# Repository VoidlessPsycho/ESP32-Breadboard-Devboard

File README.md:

# ESP32 Breadboard Devboard

This project is an ESP32-S3-WROOM-1 devboard that can fit on a breadboard, unlike standard ESP32 DevKit V1s. I made it because my current ESP32s don't fit on a breadboard and it makes it really difficult to prototype easily, so this fixes that problem.

[Journal](JOURNAL.md)

## Features
- ESP32-S3-WROOM-1 Microcontroller
- 33 GPIO Pins
- 2 3.3V Pins
- 1 VCC Pin (5-12V)
- Reset + Boot Buttons
- USB-C Receptacle
- Cool Art!

## Tech Stack:
- KiCad (PCB Design)
- Onshape (CAD Renders)
- Inkscape (SVG Art Drawing)
- VS Code (Documentation)

## Images
Schematic: \

PCB: \

CAD (Back): \

## Bill of Materials
| Manufacturer | Description | Qty | Total Price | Link |
| :--- | :--- | :---: | :--- | :--- |
| Samsung | 10uF 10V X5R 0603 Ceramic Capacitor | 6 | $0.26 | [C19702](https://jlcpcb.com/partdetail/20411-CL10A106KP8NNNC/C19702) |
| Samsung | 1uF 25V X5R 0402 Ceramic Capacitor | 2 | $0.04 | [C52923](https://jlcpcb.com/partdetail/53938-CL05A105KA5NQNC/C52923) |
| Samsung | 100nF 16V X7R 0402 Ceramic Capacitor | 6 | $0.01 | [C1525](https://jlcpcb.com/partdetail/1877-CL05B104KO5NNNC/C1525) |
| Jiangsu Changjing | B5819WSL 1A 40V SOD-123 Schottky Diode | 2 | $0.06 | [C8598](https://jlcpcb.com/partdetail/9093-B5819WSL/C8598) |
| Hubei KENTO | Red LED Water Clear 0603 | 2 | $0.01 | [C2286](https://jlcpcb.com/partdetail/Hubei_KENTOElec-KT0603R/C2286) |
| UNI-ROYAL | 0Ω 0402 Thick Film Resistor | 2 | $0.01 | [C17168](https://jlcpcb.com/partdetail/17853-0402WGF0000TCE/C17168) |
| UNI-ROYAL | 5.1kΩ 0402 1% Resistor | 4 | $0.01 | [C25905](https://jlcpcb.com/partdetail/26648-0402WGF5101TCE/C25905) |
| UNI-ROYAL | 2.2kΩ 0402 1% Resistor | 2 | $0.01 | [C25879](https://jlcpcb.com/partdetail/26622-0402WGF2201TCE/C25879) |
| UNI-ROYAL | 10kΩ 0402 1% Resistor | 4 | $0.01 | [C25744](https://jlcpcb.com/partdetail/26487-0402WGF1002TCE/C25744) |
| XUNPU | 4x3mm SMD Tactile Switch (Button) | 4 | $0.22 | [C720477](https://jlcpcb.com/partdetail/XUNPU-TS_1088AR02016/C720477) |
| STMicroelectronics| USBLC6-2SC6 SOT-23-6 ESD Protection | 5 | $0.83 | [C7519](https://jlcpcb.com/partdetail/STMicroelectronics-USBLC62SC6/C7519) |
| Advanced Monolithic | AMS1117-3.3V 1A LDO SOT-223 | 2 | $0.40 | [C6186](https://jlcpcb.com/partdetail/Advanced_MonolithicSystems-AMS1117_33/C6186) |
| Korean Hroparts | Type-C 16-Pin Female SMD USB Connector | 2 | $0.37 | [C165948](https://jlcpcb.com/partdetail/Korean_HropartsElec-TYPE_C_31_M12/C165948) |
| Espressif Systems | ESP32 Wi-Fi & Bluetooth Module | 1 | $4.77 | [C2913198](https://www.lcsc.com/product-detail/C2913198.html) |
| BOOMELE | 1x20P 2.54mm Pin Header | 5 | $0.78 | [C50981](https://www.lcsc.com/product-detail/C50981.html) |

<br>

### Manufacturing & Cost Summary

| Item / Service | Qty | Price |
| :--- | :---: | :--- |
| **PCB Manufacturing** (JLCPCB) | 5 | $2.00 |
| **PCB Assembly / PCBA** (JLCPCBA) | 2 | $19.15 |
| **Components Subtotal** | - | $7.79 |=
| JLCPCB Shipping (GSDL) | - | $3.12 |
| LCSC Shipping (GSDL) | - | $8.00 |
| LCSC Handling Fee | - | $5.00 |
| **Total Project Cost** | | **$42.82** |

---

## Motivation
I made this project to make ESP32 modules usable on a devboard. It also helped me develop my PCB skills. I also want to present my design at Open Sauce 2026.

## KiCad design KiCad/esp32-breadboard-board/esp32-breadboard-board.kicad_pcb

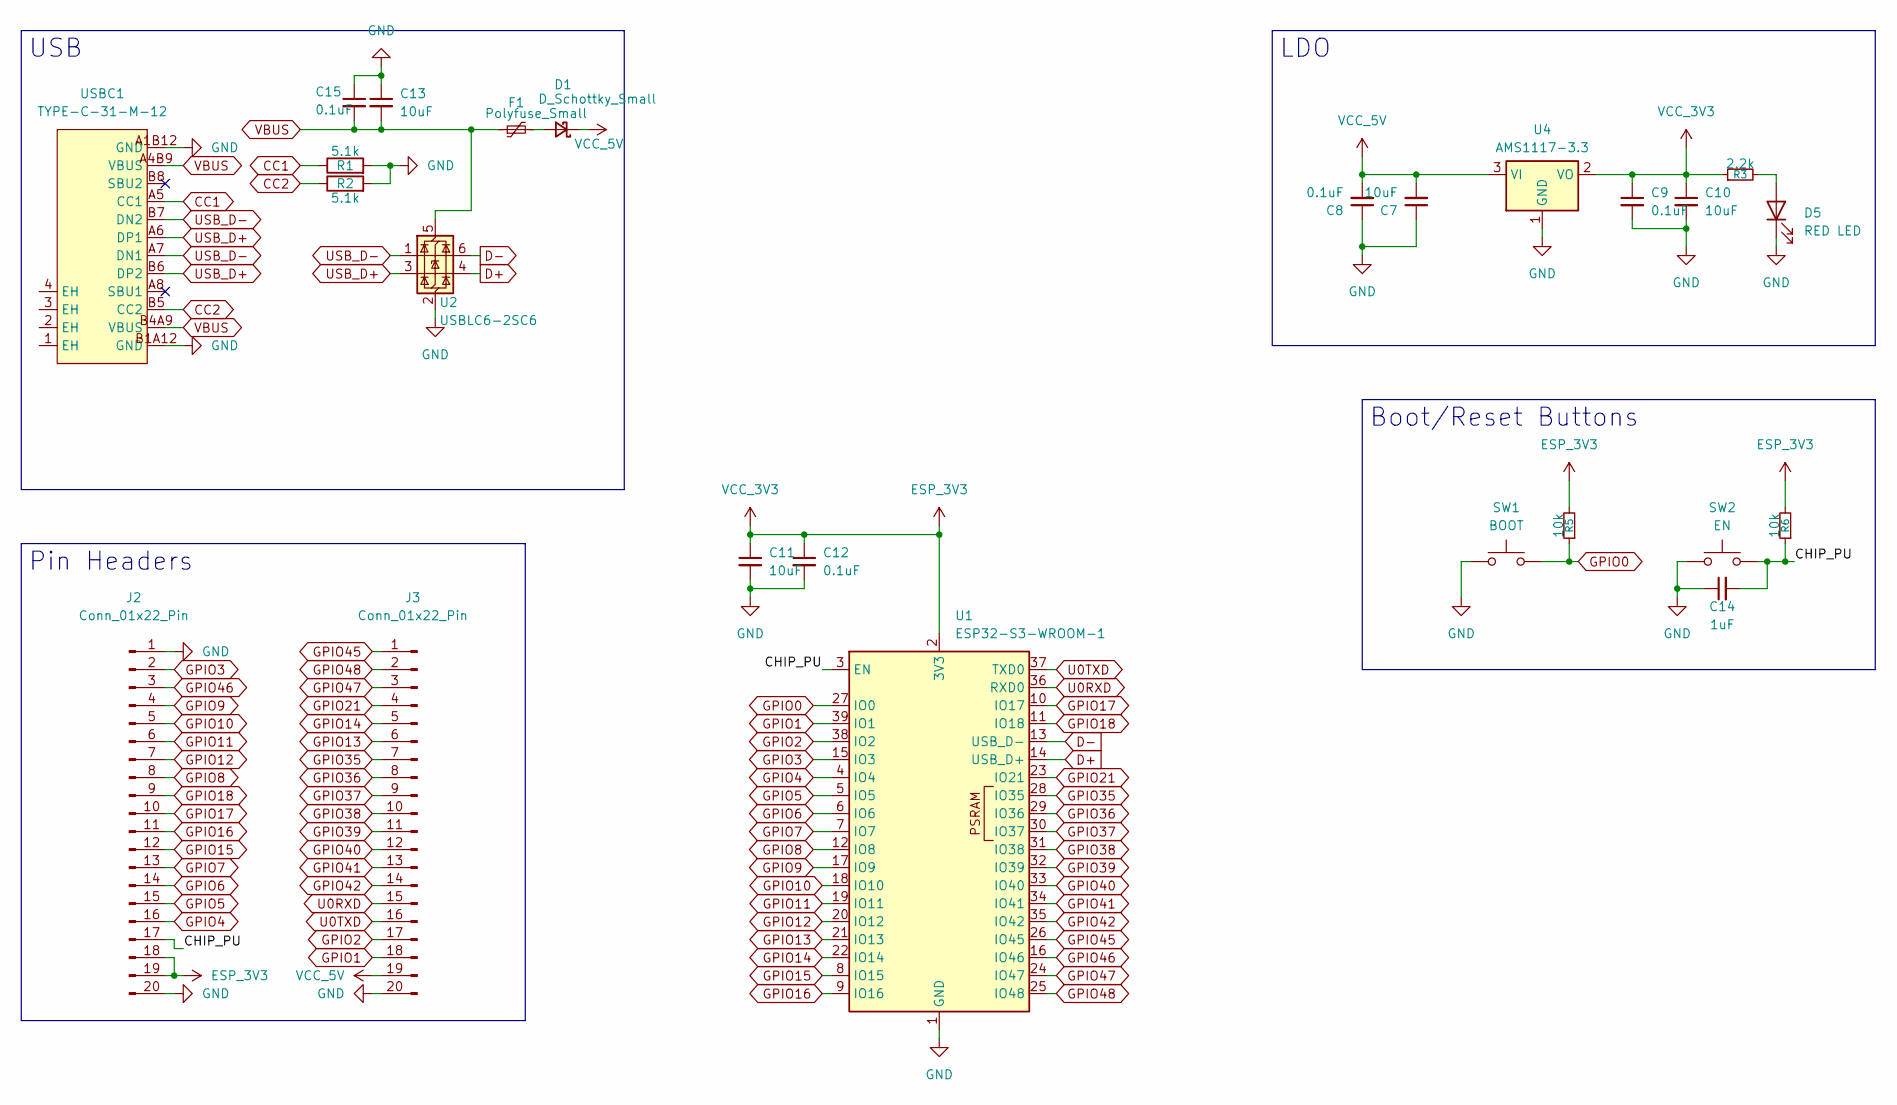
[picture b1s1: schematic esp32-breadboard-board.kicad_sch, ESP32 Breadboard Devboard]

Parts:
C7, C10, C11, C13: 10uF; C_0603_1608Metric
C8, C9, C12, C15: 0.1uF; C_0402_1005Metric
C14: 1uF; C_0402_1005Metric
D1: D_Schottky_Small; SOD-123_L2.7-W1.6-LS3.7-RD
D5: RED LED; LED_0603_1608Metric
F1: Polyfuse_Small; Fuse_0402_1005Metric
J2, J3: Conn_01x22_Pin; PinHeader_1x20_P2.54mm_Vertical
R1, R2: 5.1k; R_0402_1005Metric
R3: 2.2k; R_0402_1005Metric
R5, R6: 10k; R_0402_1005Metric
SW1: BOOT; SW-SMD_L3.9-W3.0-P4.45
SW2: EN; SW-SMD_L3.9-W3.0-P4.45
U1: ESP32-S3-WROOM-1; WIFIM-SMD_ESP32-S3-WROOM-1-N8
U2: USBLC6-2SC6; SOT-23-6
U4: AMS1117-3.3; SOT-223-3_TabPin2
USBC1: TYPE-C-31-M-12; USB-C_SMD-TYPE-C-31-M-12_1; MPN TYPE-C-31-M-12; LCSC Part C165948

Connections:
/CHIP_PU: C14.2, J2.17, R6.1, SW2.2, U1.3 (EN)
CC1: R1.1, USBC1.A5 (CC1)
CC2: R2.1, USBC1.B5 (CC2)
D+: U1.14 (USB_D+), U2.4 (I/O2)
D-: U1.13 (USB_D-), U2.6 (I/O1)
ESP_3V3: C9.1, C10.1, C11.1, C12.1, J2.18, J2.19, R3.1, R5.2, R6.2, U1.2 (3V3), U4.2 (VO)
GND: C7.1, C8.1, C9.2, C10.2, C11.2, C12.2, C13.1, C14.1, C15.1, D5.1 (K), J2.1, J2.20, J3.20, R1.2, R2.2, SW1.1, SW2.1, U1.1 (GND), U1.40 (GND), U1.41 (GND), U2.2 (GND), U4.1 (GND), USBC1.A1B12 (GND), USBC1.B1A12 (GND)
GPIO0: R5.1, SW1.2, U1.27 (IO0)
GPIO1: J3.18, U1.39 (IO1)
GPIO2: J3.17, U1.38 (IO2)
GPIO3: J2.2, U1.15 (IO3)
GPIO4: J2.16, U1.4 (IO4)
GPIO5: J2.15, U1.5 (IO5)
GPIO6: J2.14, U1.6 (IO6)
GPIO7: J2.13, U1.7 (IO7)
GPIO8: J2.8, U1.12 (IO8)
GPIO9: J2.4, U1.17 (IO9)
GPIO10: J2.5, U1.18 (IO10)
GPIO11: J2.6, U1.19 (IO11)
GPIO12: J2.7, U1.20 (IO12)
GPIO13: J3.6, U1.21 (IO13)
GPIO14: J3.5, U1.22 (IO14)
GPIO15: J2.12, U1.8 (IO15)
GPIO16: J2.11, U1.9 (IO16)
GPIO17: J2.10, U1.10 (IO17)
GPIO18: J2.9, U1.11 (IO18)
GPIO21: J3.4, U1.23 (IO21)
GPIO35: J3.7, U1.28 (IO35)
GPIO36: J3.8, U1.29 (IO36)
GPIO37: J3.9, U1.30 (IO37)
GPIO38: J3.10, U1.31 (IO38)
GPIO39: J3.11, U1.32 (IO39)
GPIO40: J3.12, U1.33 (IO40)
GPIO41: J3.13, U1.34 (IO41)
GPIO42: J3.14, U1.35 (IO42)
GPIO45: J3.1, U1.26 (IO45)
GPIO46: J2.3, U1.16 (IO46)
GPIO47: J3.3, U1.24 (IO47)
GPIO48: J3.2, U1.25 (IO48)
unnamed: D1.2 (A), F1.2
unnamed: D5.2 (A), R3.2
U0RXD: J3.15, U1.36 (RXD0)
U0TXD: J3.16, U1.37 (TXD0)
USB_D+: U2.3 (I/O2), USBC1.A6 (DP1), USBC1.B6 (DP2)
USB_D-: U2.1 (I/O1), USBC1.A7 (DN1), USBC1.B7 (DN2)
VBUS: C13.2, C15.2, F1.1, U2.5 (VBUS), USBC1.A4B9 (VBUS), USBC1.B4A9 (VBUS)
VCC_5V: C7.2, C8.2, D1.1 (K), J3.19, U4.3 (VI)

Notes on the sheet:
Boot/Reset Buttons
Pin Headers
USB
LDO

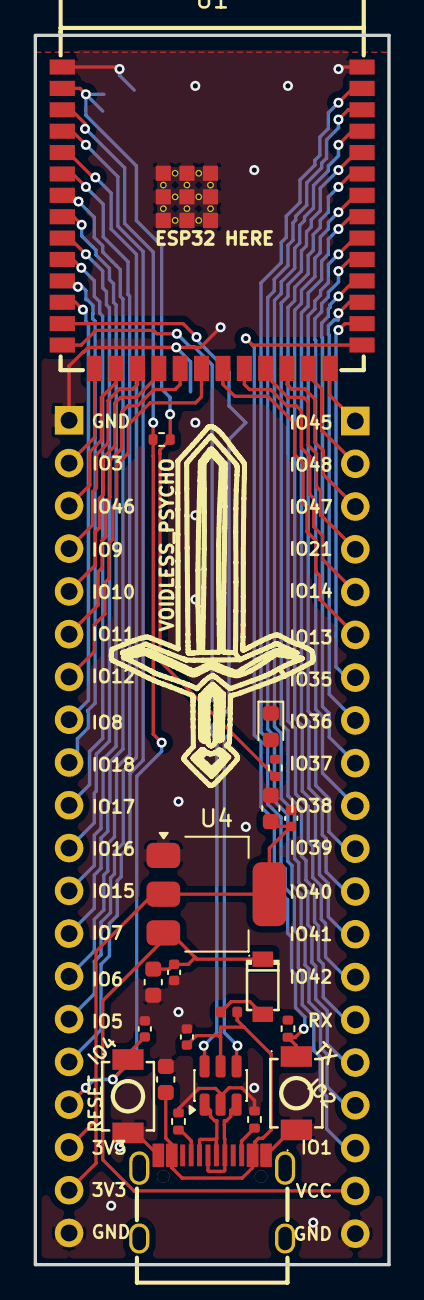
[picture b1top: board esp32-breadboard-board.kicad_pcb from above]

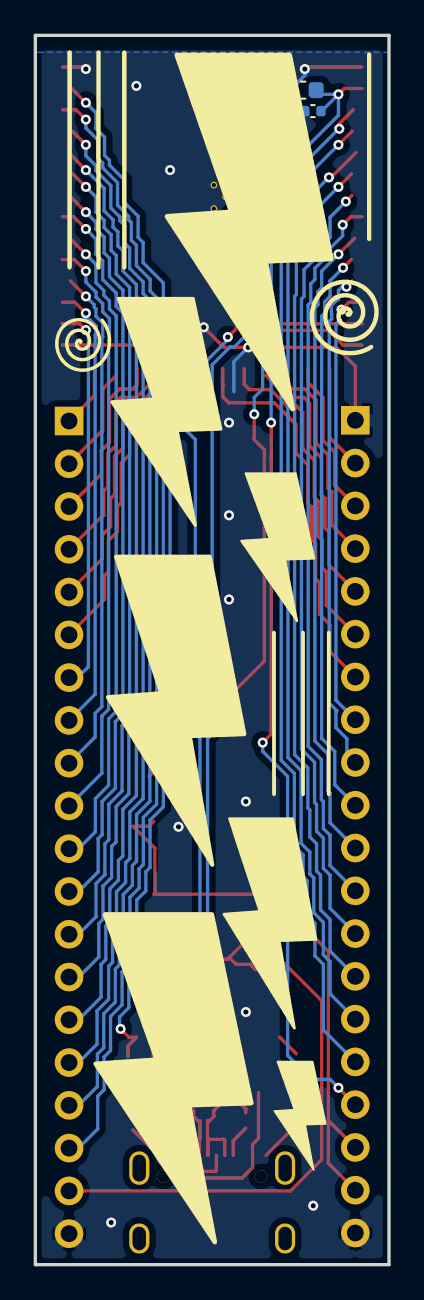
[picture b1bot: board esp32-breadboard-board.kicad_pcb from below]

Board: 2 copper layers, 21.0 x 73.0 mm, 25 parts (2 on the bottom side), 47 nets.

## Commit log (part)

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2026-06-28 Created KiCad Project
2026-06-28 Add project title to README
2026-06-28 Update README header to use Markdown format
2026-06-29 Completed Schematic
2026-06-29 Rename project from Dual Motor to Breadboard Devboard
2026-06-29 Renamed Vehicle --> Breadboard
2026-06-29 Added JOURNAL.md
2026-06-29 Updated journal
2026-06-29 Journal P2
2026-06-30 Updated Journal and PCB
2026-06-30 remove image
